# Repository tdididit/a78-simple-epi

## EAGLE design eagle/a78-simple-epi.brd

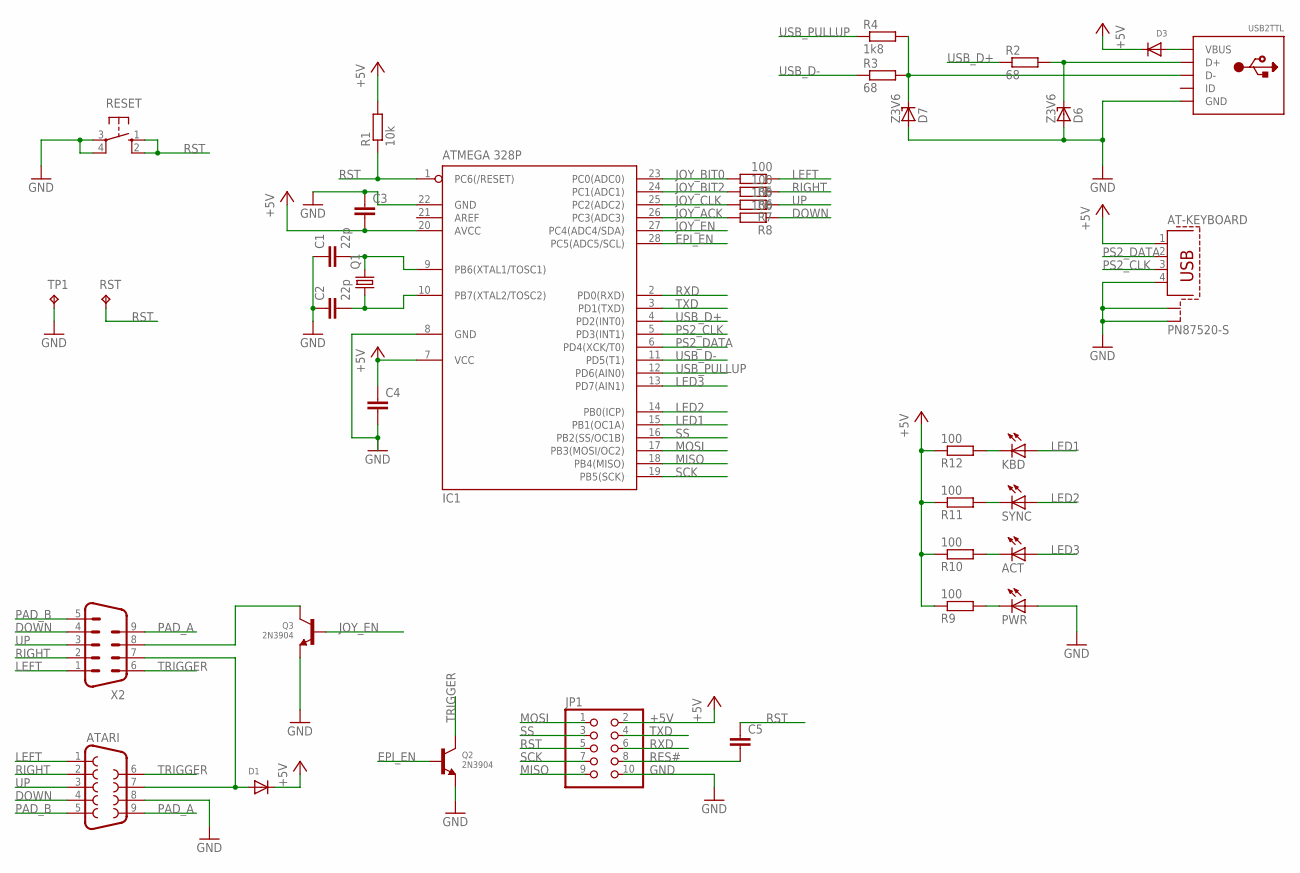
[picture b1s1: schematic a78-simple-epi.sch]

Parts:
ACT: LED3MM
AT-KEYBOARD: PN87520-S
ATARI: F09D
C1, C2: 22p; C0603
C3, C4, C5: C-EUC0603; C0603
D1, D3: DIODESOD-323F; SOD-323F
D6, D7: Z3V6; SOT23
IC1: ATMEGA 328P; DIL28-3
JP1: PINHD-2X5; 2X05
KBD: LED3MM
PWR: LED3MM
Q1: CRYSTALHC49S; HC49S
Q2, Q3: 2N3904; SOT23-R
R1: 10k; R0603
R2, R3: 68; R0603
R4: 1k8; R0603
R5, R6, R7, R8, R9, R10, R11, R12: 100; R0603
RESET: 10-XX; B3F-10XX
RST: TPB1,27; B1,27
SYNC: LED3MM
TP1: TPB1,27; B1,27
USB2TTL: USBMINIB; USB-MINIB
X2: M09D

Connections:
+5V: AT-KEYBOARD.1, C3.2, C4.1, D1.C, D3.C, IC1.7 (VCC), IC1.20 (AVCC), JP1.2, R1.2, R9.1, R10.1, R11.1, R12.1
DOWN: ATARI.4, R8.1, X2.4
EPI_EN: IC1.28 (PC5(ADC5/SCL)), Q2.1 (B)
GND: AT-KEYBOARD.4, AT-KEYBOARD.S1, AT-KEYBOARD.S2, ATARI.8, C1.1, C2.1, C3.1, C4.2, D6.1 (A), D7.1 (A), IC1.8 (GND), IC1.22 (GND), JP1.10, PWR.A, Q2.2 (E), Q3.2 (E), RESET.3, RESET.4 (P1), TP1.TP, USB2TTL.GND
JOY_ACK: IC1.26 (PC3(ADC3)), R8.2
JOY_BIT0: IC1.23 (PC0(ADC0)), R5.2
JOY_BIT2: IC1.24 (PC1(ADC1)), R6.2
JOY_CLK: IC1.25 (PC2(ADC2)), R7.2
JOY_EN: IC1.27 (PC4(ADC4/SDA)), Q3.1 (B)
LED1: IC1.15 (PB1(OC1A)), KBD.A
LED2: IC1.14 (PB0(ICP)), SYNC.A
LED3: ACT.A, IC1.13 (PD7(AIN1))
LEFT: ATARI.1, R5.1, X2.1
MISO: IC1.18 (PB4(MISO)), JP1.9
MOSI: IC1.17 (PB3(MOSI/OC2)), JP1.1
unnamed: Q3.3 (C), X2.8
unnamed: PWR.K (C), R9.2
unnamed: ACT.K (C), R10.2
unnamed: R11.2, SYNC.K (C)
unnamed: KBD.K (C), R12.2
unnamed: D7.3 (C), R3.2, R4.2, USB2TTL.D-
unnamed: D3.A, USB2TTL.VBUS
unnamed: D6.3 (C), R2.2, USB2TTL.D+
unnamed: ATARI.7, D1.A, X2.7
unnamed: C1.2, IC1.9 (PB6(XTAL1/TOSC1)), Q1.2
unnamed: C2.2, IC1.10 (PB7(XTAL2/TOSC2)), Q1.1
PAD_A: ATARI.9, X2.9
PAD_B: ATARI.5, X2.5
PS2_CLK: AT-KEYBOARD.3, IC1.5 (PD3(INT1))
PS2_DATA: AT-KEYBOARD.2, IC1.6 (PD4(XCK/T0))
RES#: C5.2, JP1.8
RIGHT: ATARI.2, R6.1, X2.2
RST: C5.1, IC1.1 (PC6(/RESET)), JP1.5, R1.1, RESET.1 (S), RESET.2 (S1), RST.TP
RXD: IC1.2 (PD0(RXD)), JP1.6
SCK: IC1.19 (PB5(SCK)), JP1.7
SS: IC1.16 (PB2(SS/OC1B)), JP1.3
TRIGGER: ATARI.6, Q2.3 (C), X2.6
TXD: IC1.3 (PD1(TXD)), JP1.4
UP: ATARI.3, R7.1, X2.3
USB_D+: IC1.4 (PD2(INT0)), R2.1
USB_D-: IC1.11 (PD5(T1)), R3.1
USB_PULLUP: IC1.12 (PD6(AIN0)), R4.1

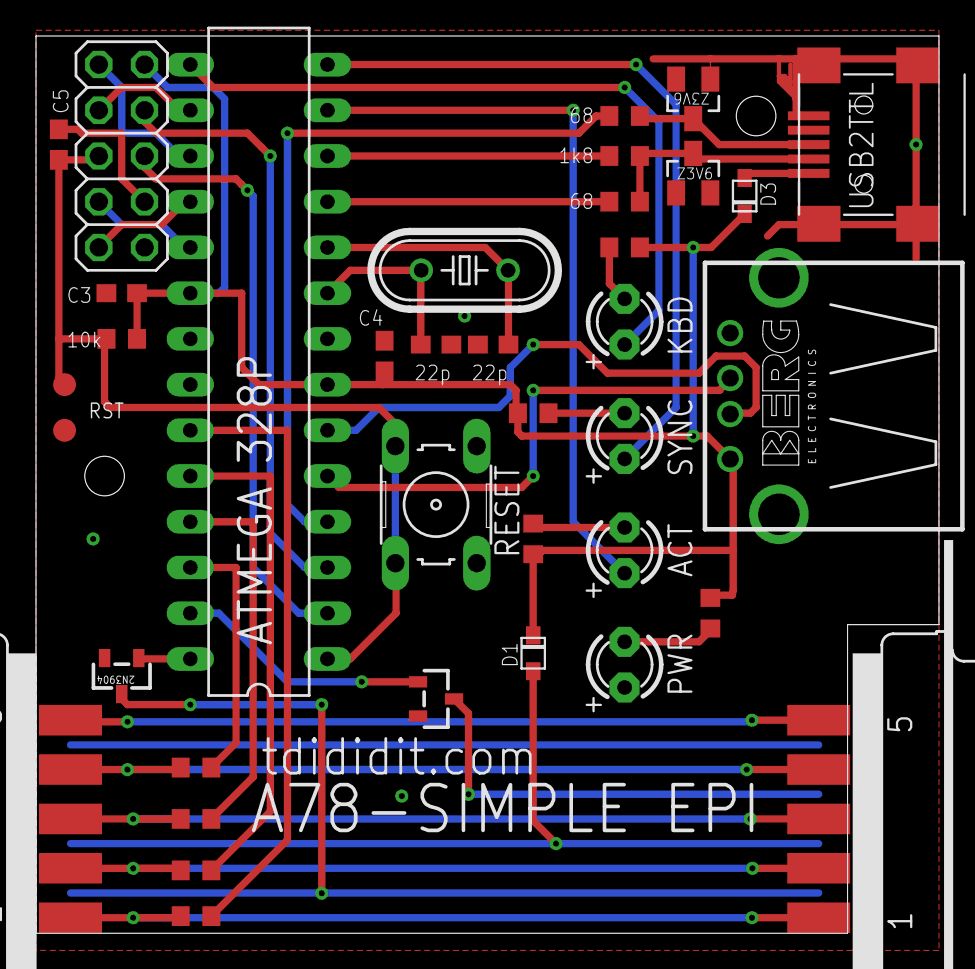
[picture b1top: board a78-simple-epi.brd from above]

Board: 2 copper layers, 50.2 x 49.8 mm, 37 parts (0 on the bottom side), 42 nets.

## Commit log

2016-03-20 :lollipop: Added .gitattributes
2016-03-20 eagle and sketchup files
2016-03-20 patch

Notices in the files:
parts and their libraries:
microbuilder: This work is placed in the public domain, and may be freely used for commercial and non-commercial work with the following conditions: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
